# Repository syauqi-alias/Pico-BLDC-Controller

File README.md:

# Pico-BLDC-Controller

This project documents the design of a custom Brushless DC (BLDC) motor controller for a hotplate magnetic stirrer, intended for integration with an Opentrons automated liquid handling robot at the Manufacturing Future Lab, University College London.

---

## Project Overview

The primary goal is to create an open-source, accessible, and robust controller for a **260W 30V/7A Maxon BLDC motor**. This is my first venture into designing a motor controller, especially one involving a three-phase half-bridge topology. The journey is as much about learning as it is about the final product.

---

## Hardware Design

The schematic design is functionally complete and is currently undergoing peer review. The component selection process prioritized simplicity and a reduced component count to make the design easier to understand and replicate.

### Key Components:

* **Microcontroller:** **Raspberry Pi RP2350**
    * Chosen for its straightforward development environment and strong community support. While the ADC conversion speed can be a limitation for high-performance Field-Oriented Control (FOC), the goal is to create a baseline design that the open-source community can build upon and optimize.

* **Pre-driver:** **Texas Instruments DRV8350S**
    * This integrated gate driver significantly simplifies the design by handling much of the complexity associated with driving MOSFETs, such as the need for external charge pumps or bootstrap components. It reduces the overall component count and circuit complexity.

* **Motor:** **Maxon EC 90 flat Ø90 mm, brushless, 260 W, with Hall sensors**
    * A powerful 260W brushless motor, providing more than enough torque for stirring viscous solutions.

---

## Software and Firmware

The initial firmware will be developed using the **[simpleFOC](https://simplefoc.com/)** library to accelerate development and establish a functional baseline.

Once the hardware is validated, a longer-term goal is to develop custom firmware from scratch to fully optimize the controller's performance for this specific application.

---

## Current Status

**Status:** In Development (Last Updated: 29/08/2025)

* [x] Component selection finalized.
* [x] Initial schematic design complete.
* [x] Schematic peer review in progress.
* [x] PCB layout design.
* [X] PCB peer review 
* [X] Send out PCB to manufacturer
* [ ] Prototyping and hardware testing.
* [ ] Firmware development.

I'm actively seeking feedback on the schematic from colleagues and online forums. The design has evolved significantly through this iterative process, and I'll continue to post updates as the project progresses.

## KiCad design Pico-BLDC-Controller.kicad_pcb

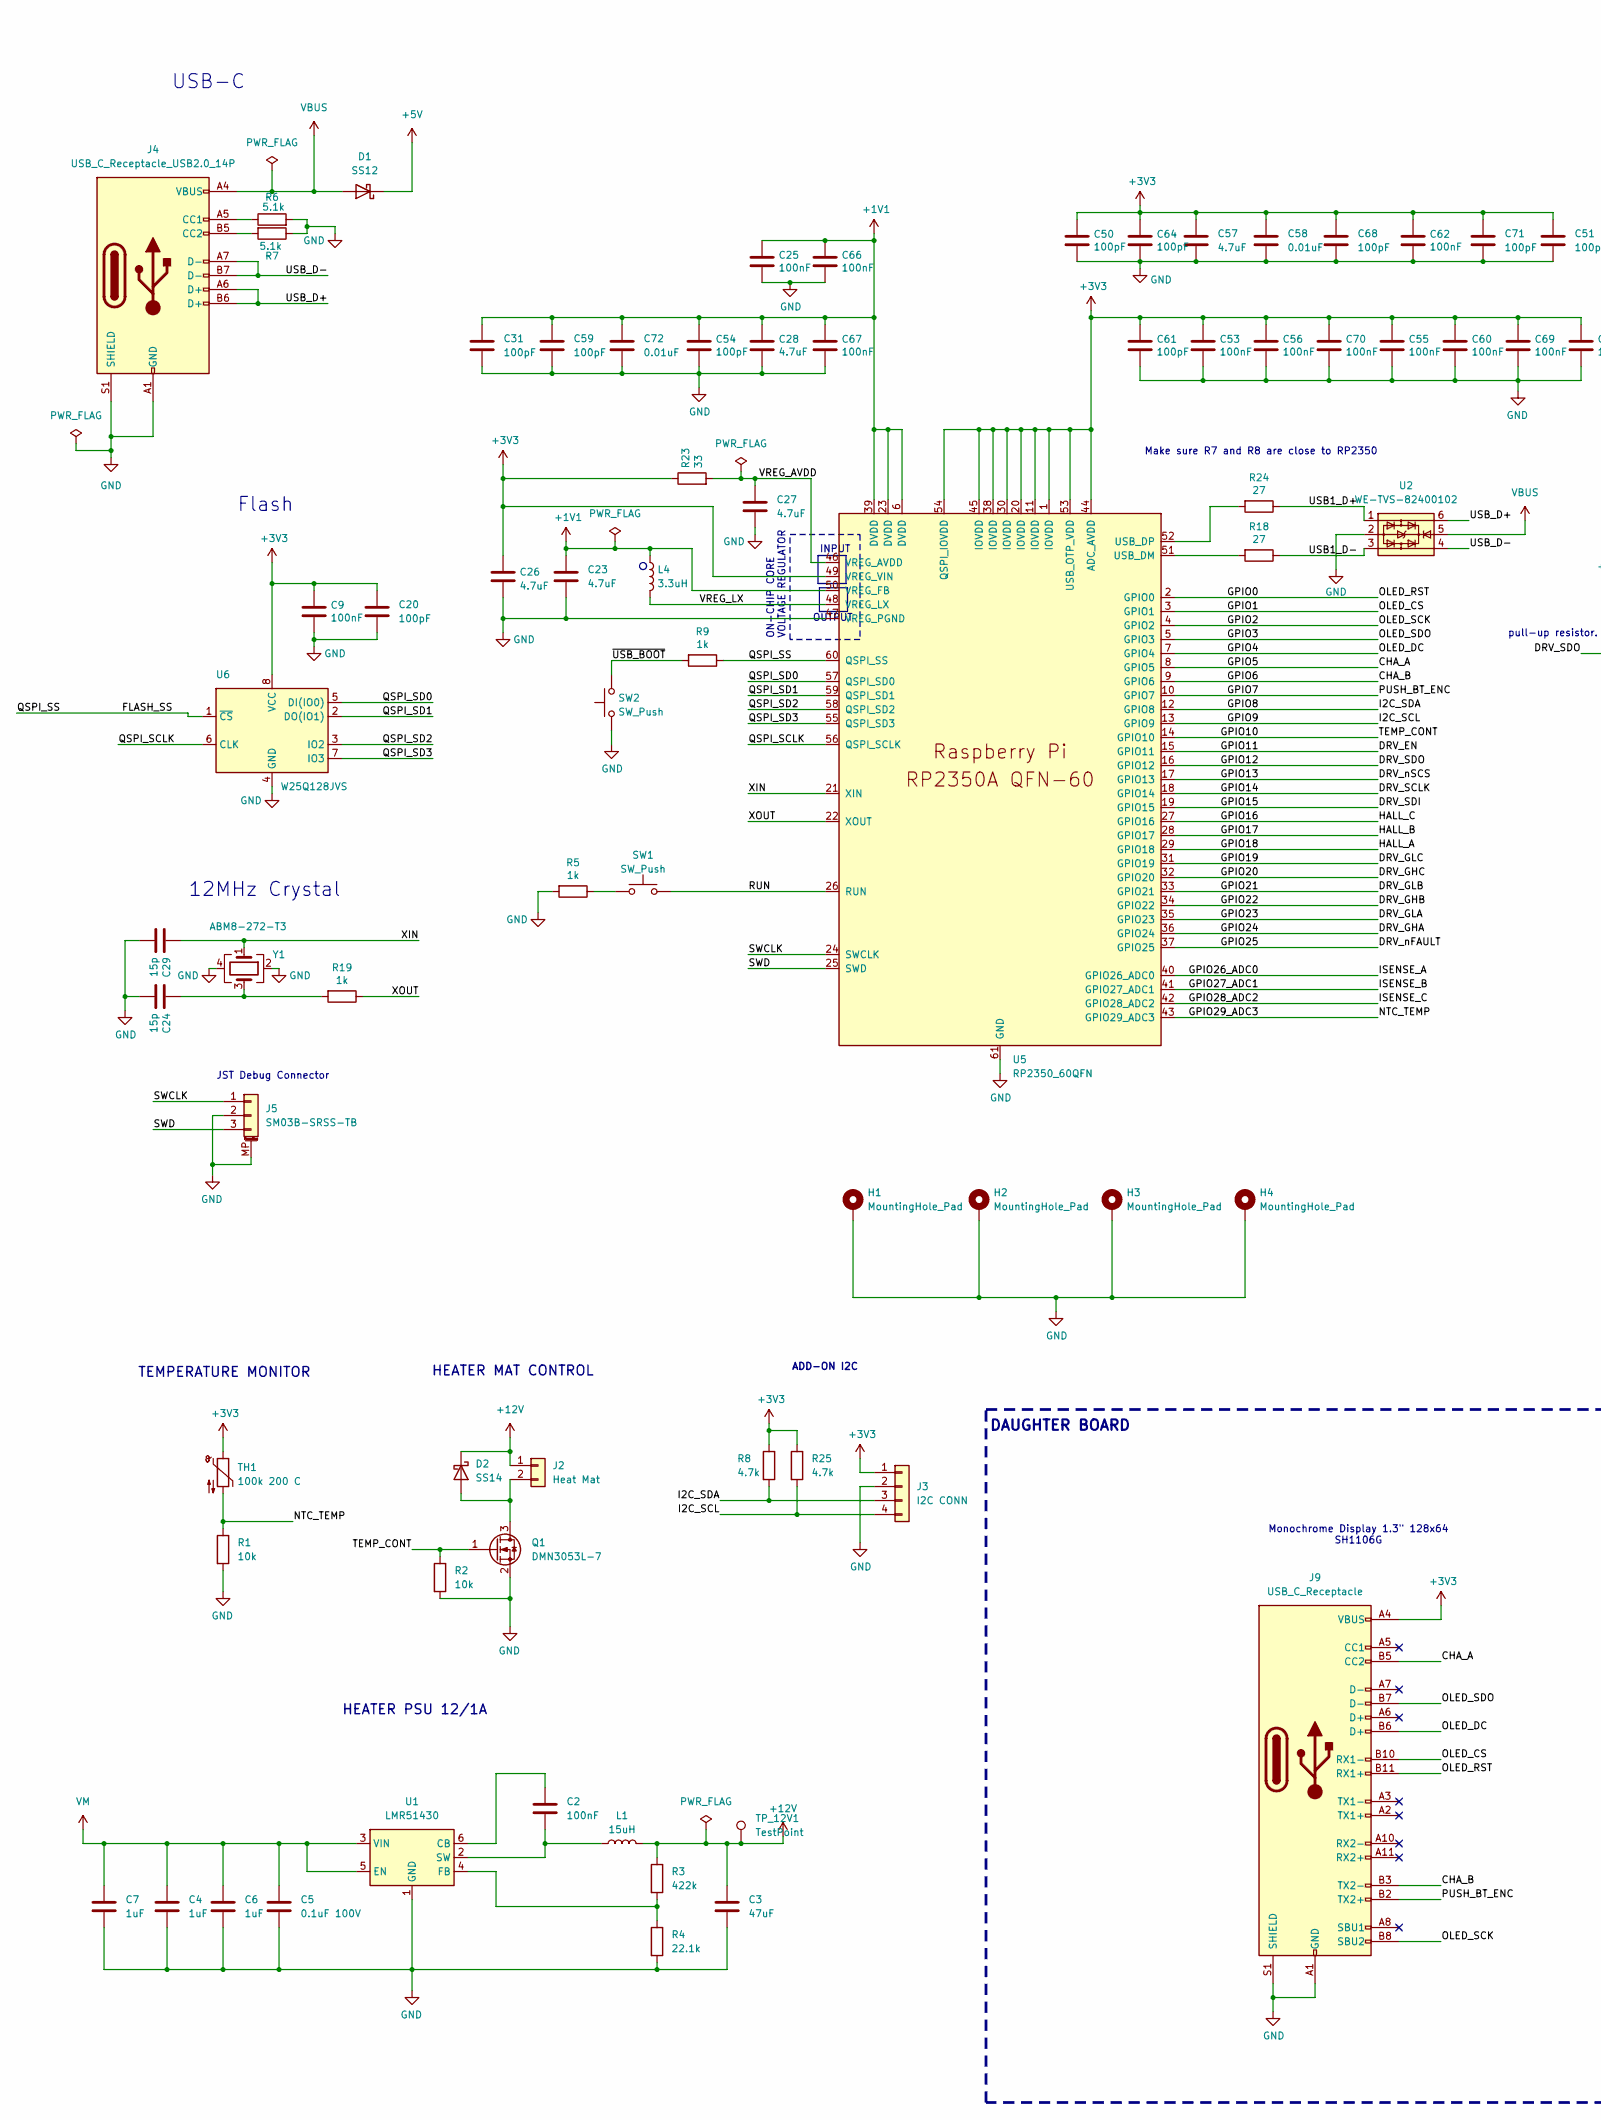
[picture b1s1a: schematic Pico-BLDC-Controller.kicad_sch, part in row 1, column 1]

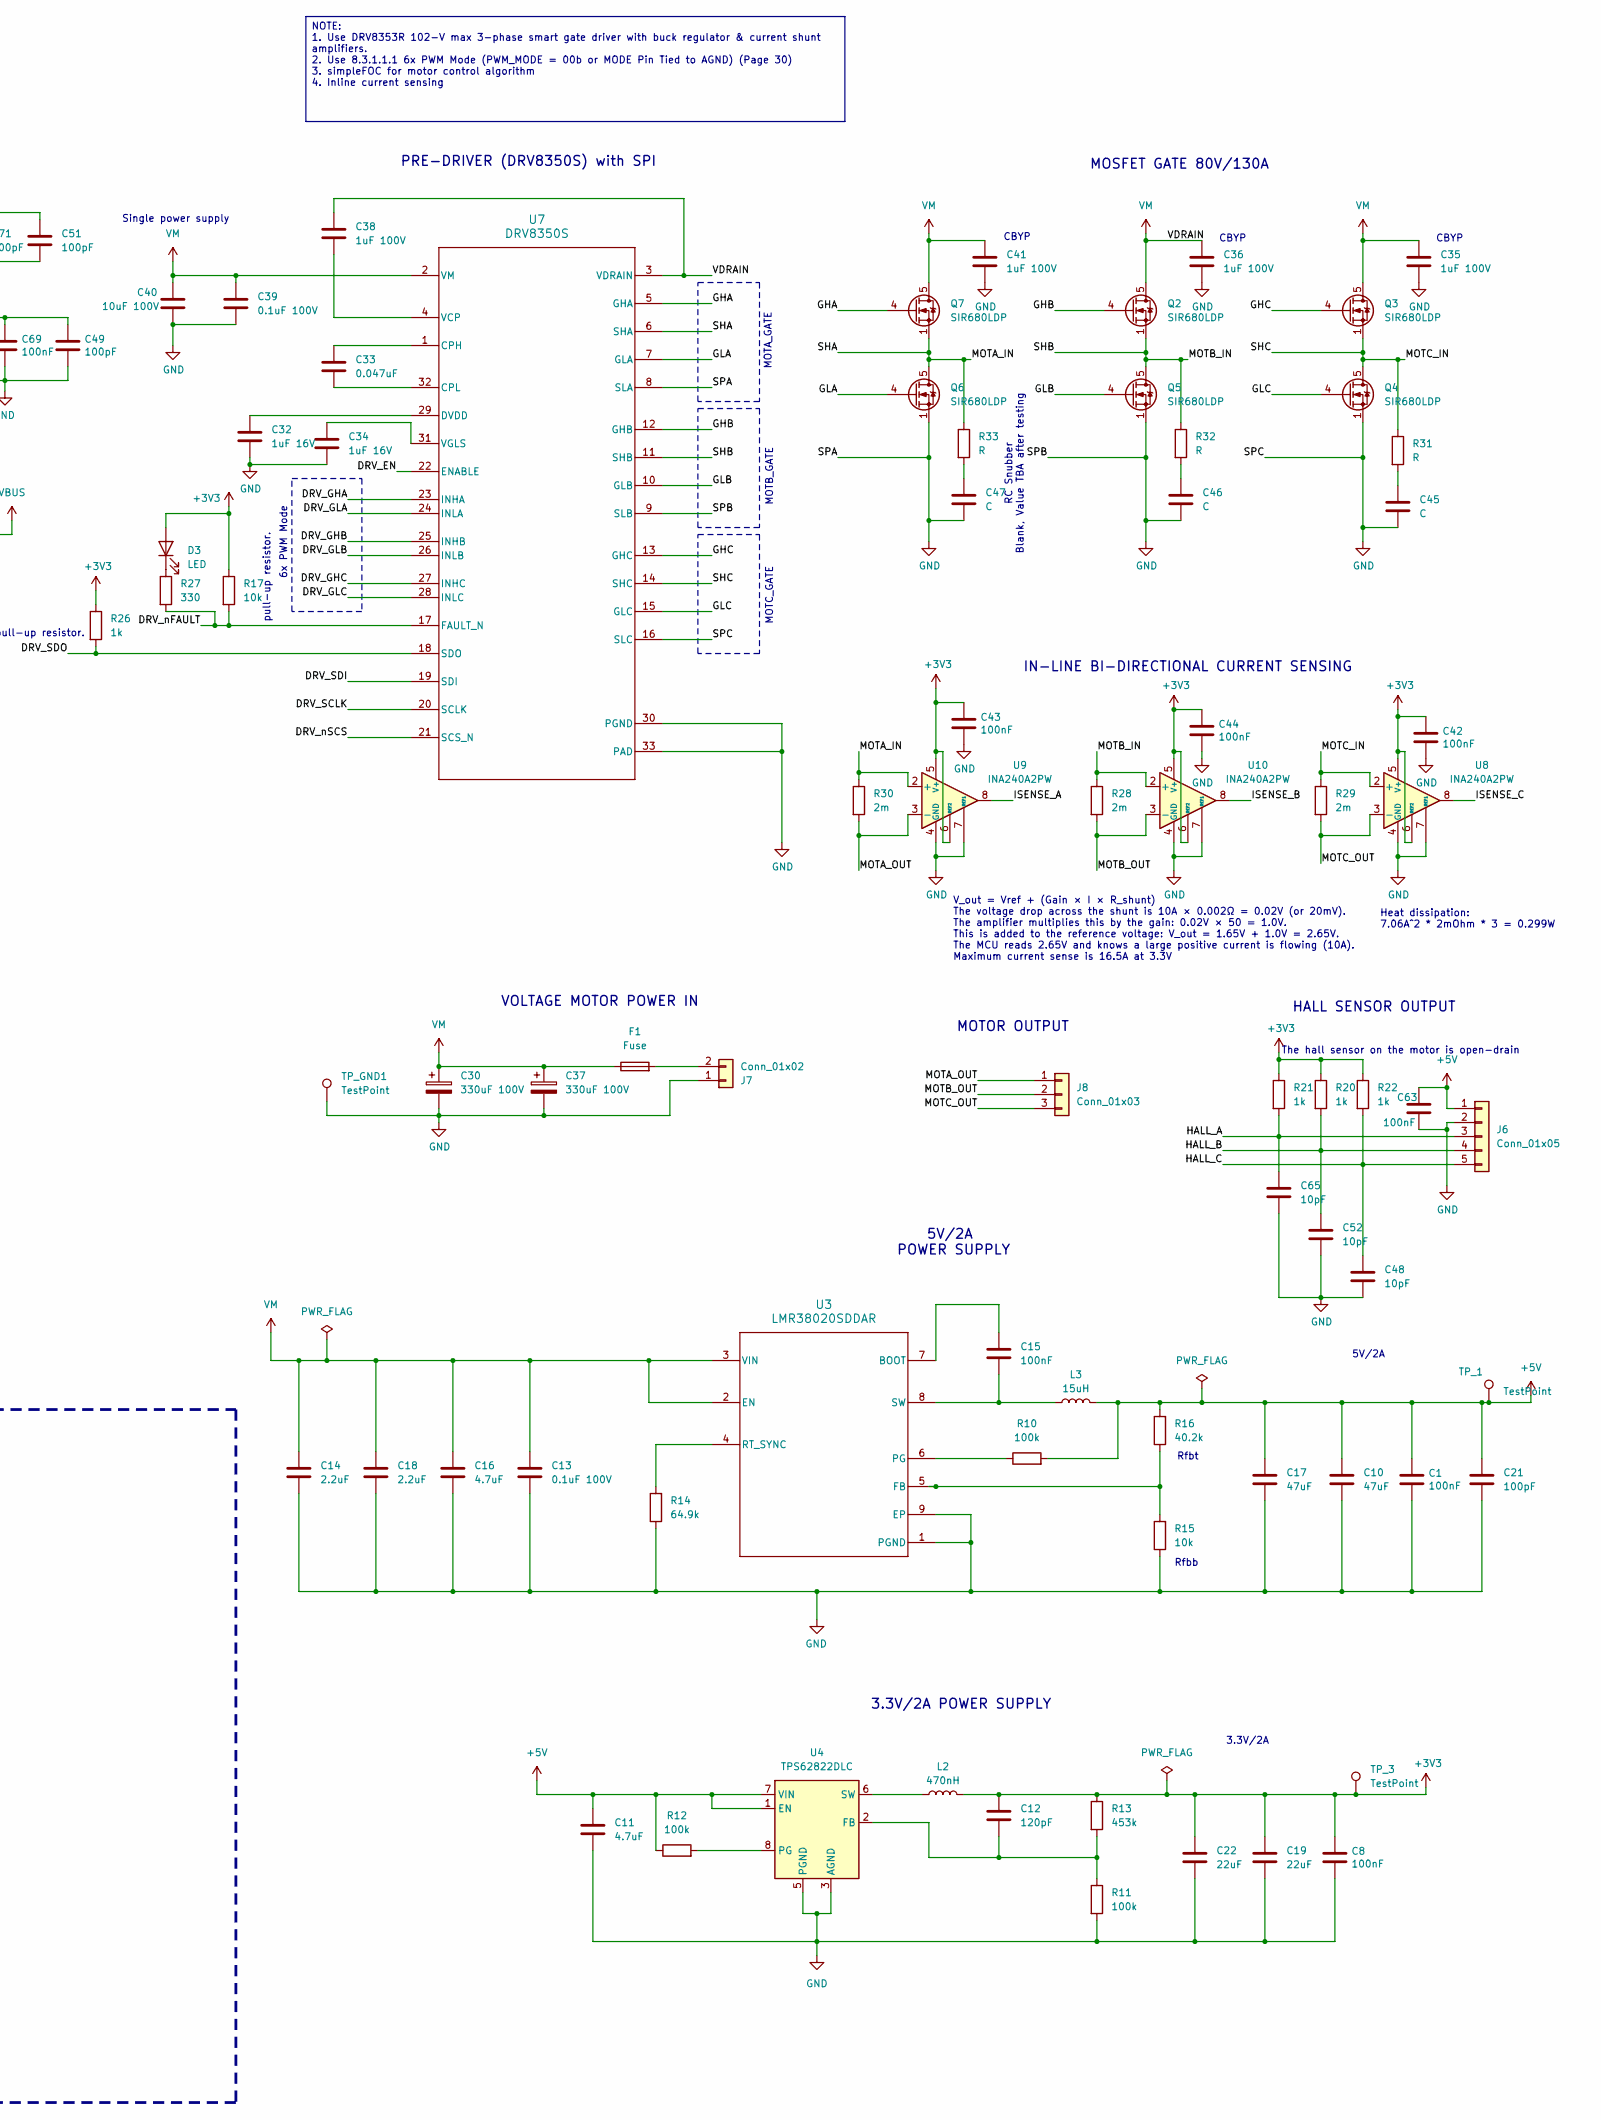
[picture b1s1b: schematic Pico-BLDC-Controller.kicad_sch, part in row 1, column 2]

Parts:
C1, C2, C8, C9, C15, C25, C42, C43, C44, C53, C55, C56, C60, C62, C63, C66, C67, C69, C70: 100nF; C_0603_1608Metric_Pad1.08x0.95mm_HandSolder; MPN C0603C104K5RACAUTO
C3, C10, C17: 47uF; C_1210_3225Metric_Pad1.33x2.70mm_HandSolder; MPN GRM32ER61C476KE15L
C4, C6, C7: 1uF; R_0603_1608Metric_Pad0.98x0.95mm_HandSolder; MPN GRM188D72A105KE01J
C5, C13, C39: 0.1uF 100V; C_0603_1608Metric_Pad1.08x0.95mm_HandSolder; MPN HMK107B7104KAHT
C11, C23, C26, C27, C28: 4.7uF; C_0603_1608Metric_Pad1.08x0.95mm_HandSolder; MPN MCASL168BD7475KTCA01
C12: 120pF; C_0603_1608Metric_Pad1.08x0.95mm_HandSolder; MPN KGM15ACG1H121JT
C14, C18: 2.2uF; C_1210_3225Metric; MPN HMK325B7225KN-T
C16: 4.7uF; C_1210_3225Metric; MPN KAM32LR72A475KU
C19, C22: 22uF; C_0603_1608Metric_Pad1.08x0.95mm_HandSolder; MPN GRM188R60J226MEA0D
C20, C31, C49, C50, C51, C54, C59, C61, C64, C68, C71: 100pF; C_0603_1608Metric_Pad1.08x0.95mm_HandSolder; MPN 0603YC101KAT2A
C21: 100pF; C_0603_1608Metric_Pad1.08x0.95mm_HandSolder; MPN C0402C101K3RACAUTO
C24, C29: 15p; C_0603_1608Metric_Pad1.08x0.95mm_HandSolder; MPN 06033A150JAT2A
C30, C37: 330uF 100V; EEEFK0J103SM; MPN EEV-FK2A331M
C32, C34: 1uF 16V; C_0603_1608Metric_Pad1.08x0.95mm_HandSolder; MPN GXT188R71C105KE13D
C33: 0.047uF; C_0805_2012Metric_Pad1.18x1.45mm_HandSolder; MPN C2012X7R2A473K125AA
C35, C36, C38, C41: 1uF 100V; C_1206_3216Metric; MPN CL31B105KCHNNNE
C40: 10uF 100V; C_2220_5750Metric_Pad1.97x5.40mm_HandSolder; MPN CGA9N3X7S2A106K230KE
C45, C46, C47: C; C_0603_1608Metric_Pad1.08x0.95mm_HandSolder
C48, C52, C65: 10pF; C_0603_1608Metric_Pad1.08x0.95mm_HandSolder; MPN 06033A100KAT2A
C57: 4.7uF; C_0603_1608Metric_Pad1.08x0.95mm_HandSolder; MPN KGM15BR50J475KT
C58, C72: 0.01uF; C_0603_1608Metric_Pad1.08x0.95mm_HandSolder; MPN GCM188R71H103KA37J
D1: SS12; D_SMA; MPN SS12
D2: SS14; D_SMA; MPN SS14
D3: LED; LED_0603_1608Metric_Pad1.05x0.95mm_HandSolder
F1: Fuse; Fuse_Schurter_UMZ250; MPN 0463030.ER
H1, H2, H3, H4: MountingHole_Pad; MountingHole_2.2mm_M2_DIN965_Pad_TopBottom
J2: Heat Mat; Molex_KK-254_AE-6410-02A_1x02_P2.54mm_Vertical; MPN 217796-1021
J3: I2C CONN; Molex_KK-254_AE-6410-04A_1x04_P2.54mm_Vertical; MPN 22-11-2042
J4: USB_C_Receptacle_USB2.0_14P; USB_C_Receptacle_HRO_TYPE-C-31-M-12; MPN TYPE-C-31-M-12
J5: SM03B-SRSS-TB; JST_SH_SM03B-SRSS-TB_1x03-1MP_P1.00mm_Horizontal; MPN SM03B-SRSS-TB(LF)(SN)
J6: Conn_01x05; Molex_KK-254_AE-6410-05A_1x05_P2.54mm_Vertical; MPN 22-11-2052
J7: Conn_01x02; AMASS_XT30U-M_1x02_P5.0mm_Vertical; MPN XT30U-M
J8: Conn_01x03; AMASS_MR30PW-FB_1x03_P3.50mm_Horizontal; MPN MR30PW-F20.G.Y
J9: USB_C_Receptacle; USB_C_Receptacle_JAE_DX07S024WJ3R400
L1: 15uH; L_Coilcraft_MSS1210-XXX; MPN MSS1210-153MED
L2: 470nH; L_Wurth_WE-LQSH-2010; MPN 74479275147
L3: 15uH; L_Coilcraft_MSS1038-XXX; MPN MSS1038-153MLB
L4: 3.3uH; L_pol_2016; MPN AOTA-B201610S3R3-101-T
Q1: DMN3053L-7; SOT-23; MPN DMN3053L-7
Q2, Q3, Q4, Q5, Q6, Q7: SIR680LDP; PowerPAK_SO-8_Single; MPN SIR680LDP
R1, R2, R17: 10k; R_0603_1608Metric_Pad0.98x0.95mm_HandSolder; MPN AC0603JR-7W10KL
R3: 422k; R_0603_1608Metric_Pad0.98x0.95mm_HandSolder; MPN ERJ-3EKF4223V
R4: 22.1k; R_0603_1608Metric_Pad0.98x0.95mm_HandSolder; MPN CRCW060322K1FKEBC
R5, R9, R19, R20, R21, R22, R26: 1k; R_0603_1608Metric_Pad0.98x0.95mm_HandSolder; MPN RC0603FR-101KL
R6, R7: 5.1k; R_0603_1608Metric_Pad0.98x0.95mm_HandSolder; MPN CR0603-FX-5101ELF
R8, R25: 4.7k; R_0603_1608Metric_Pad0.98x0.95mm_HandSolder; MPN RC0603FR-7W4K7L
R10, R11: 100k; R_0603_1608Metric_Pad0.98x0.95mm_HandSolder; MPN CRCW0603100KFKEA
R12: 100k; R_0603_1608Metric; MPN ERJ-PB3B1003V
R13: 453k; R_0603_1608Metric_Pad0.98x0.95mm_HandSolder; MPN CR0603-FX-4533ELF
R14: 64.9k; R_0603_1608Metric_Pad0.98x0.95mm_HandSolder; MPN CRCW060364K9FKEA
R15: 10k; R_0603_1608Metric_Pad0.98x0.95mm_HandSolder; MPN CRCW060310K0FKEI
R16: 40.2k; R_0603_1608Metric_Pad0.98x0.95mm_HandSolder; MPN CR0603-FX-4022ELF
R18, R24: 27; R_0603_1608Metric_Pad0.98x0.95mm_HandSolder; MPN CR0603-JW-270ELF
R23: 33; R_0603_1608Metric_Pad0.98x0.95mm_HandSolder; MPN AC0603DR-0733RL
R27: 330; R_0603_1608Metric; MPN CRCW0603330RFKEC
R28, R29, R30: 2m; R_2512_6332Metric_Pad1.40x3.35mm_HandSolder; MPN WSLP25122L000FEA
R31, R32, R33: R; R_0805_2012Metric_Pad1.20x1.40mm_HandSolder
SW1, SW2: SW_Push; SW_Push_1P1T_NO_Vertical_Wuerth_434133025816; MPN 434133025816
TH1: 100k 200 C; PinSocket_1x02_P2.54mm_Vertical; MPN B57560G1104F000
TP_1, TP_3, TP_12V1: TestPoint; TestPoint_Pad_D1.0mm
TP_GND1: TestPoint; TestPoint_Pad_D1.0mm
U1: LMR51430; SOT-23-6; MPN LMR51430YFDDCR
U2: WE-TVS-82400102; SOT-23-6; MPN 82400102
U3: LMR38020SDDAR; DDA0008E-MFG; MPN LMR38020SDDAR
U4: TPS62822DLC; Texas_VSON-HR-8_1.5x2mm_P0.5mm; MPN TPS62822DLCR
U5: RP2350_60QFN; RP2350-QFN-60-1EP_7x7_P0.4mm_EP3.4x3.4mm_ThermalVias; MPN SC1509(13)
U6: W25Q128JVS; SOIC-8_5.3x5.3mm_P1.27mm; MPN W25Q128JVSIM TR
U7: DRV8350S; RTV0032E; MPN DRV8350SRTVT
U8, U9, U10: INA240A2PW; TSSOP-8_4.4x3mm_P0.65mm; MPN INA240A2PWR
Y1: ABM8-272-T3; Crystal_SMD_3225-4Pin_3.2x2.5mm; MPN ABM8-272-T3

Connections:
+1V1: C23.1, C25.1, C28.1, C31.1, C54.1, C59.1, C66.1, C67.1, C72.1, L4.1, U5.6 (DVDD), U5.23 (DVDD), U5.39 (DVDD), U5.50 (VREG_FB)
+3V3: C8.1, C9.1, C12.1, C19.1, C20.1, C22.1, C26.1, C42.1, C43.1, C44.1, C49.1, C50.1, C51.1, C53.1, C55.1, C56.1, C57.1, C58.1, C60.1, C61.1, C62.1, C64.1, C68.1, C69.1, C70.1, C71.1, D3.2 (A), J3.1, J9.A4 (VBUS), J9.A9 (VBUS), J9.B4 (VBUS), J9.B9 (VBUS), L2.2, R8.1, R13.1, R17.1, R20.1, R21.1, R22.1, R23.1, R25.1, R26.1, TH1.1, TP_3.1, U5.1 (IOVDD), U5.11 (IOVDD), U5.20 (IOVDD), U5.30 (IOVDD), U5.38 (IOVDD), U5.44 (ADC_AVDD), U5.45 (IOVDD), U5.49 (VREG_VIN), U5.53 (USB_OTP_VDD), U5.54 (QSPI_IOVDD), U6.8 (VCC), U8.5 (V+), U8.6 (REF2), U9.5 (V+), U9.6 (REF2), U10.5 (V+), U10.6 (REF2)
+5V: C1.1, C10.1, C11.1, C17.1, C21.1, C63.1, D1.1 (K), J6.1, L3.2, R10.2, R12.1, R16.2, TP_1.1, U4.1 (EN), U4.7 (VIN)
+12V: C3.1, D2.1 (K), J2.1, L1.2, R3.1, TP_12V1.1
/CHA_A: J9.B5 (CC2), U5.8 (GPIO5)
/CHA_B: J9.B3 (TX2-), U5.9 (GPIO6)
/DRV_EN: U5.15 (GPIO11), U7.22 (ENABLE)
/DRV_GHA: U5.36 (GPIO24), U7.23 (INHA)
/DRV_GHB: U5.34 (GPIO22), U7.25 (INHB)
/DRV_GHC: U5.32 (GPIO20), U7.27 (INHC)
/DRV_GLA: U5.35 (GPIO23), U7.24 (INLA)
/DRV_GLB: U5.33 (GPIO21), U7.26 (INLB)
/DRV_GLC: U5.31 (GPIO19), U7.28 (INLC)
/DRV_SCLK: U5.18 (GPIO14), U7.20 (SCLK)
/DRV_SDI: U5.19 (GPIO15), U7.19 (SDI)
/DRV_SDO: R26.2, U5.16 (GPIO12), U7.18 (SDO)
/DRV_nFAULT: R17.2, R27.2, U5.37 (GPIO25), U7.17 (FAULT_N)
/DRV_nSCS: U5.17 (GPIO13), U7.21 (SCS_N)
/FLASH_SS: R9.1, U5.60 (QSPI_SS), U6.1 (~CS)
/GHA: Q7.4 (G), U7.5 (GHA)
/GHB: Q2.4 (G), U7.12 (GHB)
/GHC: Q3.4 (G), U7.13 (GHC)
/GLA: Q6.4 (G), U7.7 (GLA)
/GLB: Q5.4 (G), U7.10 (GLB)
/GLC: Q4.4 (G), U7.15 (GLC)
/GPIO0: J9.B11 (RX1+), U5.2 (GPIO0)
/GPIO1: J9.B10 (RX1-), U5.3 (GPIO1)
/GPIO2: J9.B8 (SBU2), U5.4 (GPIO2)
/GPIO3: J9.B7 (D-), U5.5 (GPIO3)
/GPIO4: J9.B6 (D+), U5.7 (GPIO4)
/GPIO7: J9.B2 (TX2+), U5.10 (GPIO7)
/GPIO8: J3.3, R8.2, U5.12 (GPIO8)
/GPIO9: J3.4, R25.2, U5.13 (GPIO9)
/GPIO10: Q1.1 (G), R2.1, U5.14 (GPIO10)
/GPIO16: C48.1, J6.5, R22.2, U5.27 (GPIO16)
/GPIO17: C52.1, J6.4, R20.2, U5.28 (GPIO17)
/GPIO18: C65.1, J6.3, R21.2, U5.29 (GPIO18)
/GPIO26_ADC0: U5.40 (GPIO26_ADC0), U9.8
/GPIO27_ADC1: U5.41 (GPIO27_ADC1), U10.8
/GPIO28_ADC2: U5.42 (GPIO28_ADC2), U8.8
/GPIO29_ADC3: R1.1, TH1.2, U5.43 (GPIO29_ADC3)
/MOTA_IN: Q6.5 (D), Q7.1 (S), Q7.2 (S), Q7.3 (S), R30.1, R33.1, U7.6 (SHA), U9.2 (+)
/MOTA_OUT: J8.1, R30.2, U9.3 (-)
/MOTB_IN: Q2.1 (S), Q2.2 (S), Q2.3 (S), Q5.5 (D), R28.1, R32.1, U7.11 (SHB), U10.2 (+)
/MOTB_OUT: J8.2, R28.2, U10.3 (-)
/MOTC_IN: Q3.1 (S), Q3.2 (S), Q3.3 (S), Q4.5 (D), R29.1, R31.1, U7.14 (SHC), U8.2 (+)
/MOTC_OUT: J8.3, R29.2, U8.3 (-)
/QSPI_SCLK: U5.56 (QSPI_SCLK), U6.6 (CLK)
/QSPI_SD0: U5.57 (QSPI_SD0), U6.5 (DI(IO0))
/QSPI_SD1: U5.59 (QSPI_SD1), U6.2 (DO(IO1))
/QSPI_SD2: U5.58 (QSPI_SD2), U6.3 (IO2)
/QSPI_SD3: U5.55 (QSPI_SD3), U6.7 (IO3)
/RUN: SW1.2, U5.26 (RUN)
/SWCLK: J5.1, U5.24 (SWCLK)
/SWD: J5.3, U5.25 (SWD)
/USB1_D+: R24.1, U2.1
/USB1_D-: R18.1, U2.3
/USB_D+: J4.A6 (D+), J4.B6 (D+), U2.6
/USB_D-: J4.A7 (D-), J4.B7 (D-), U2.4
/VREG_AVDD: C27.1, R23.2, U5.46 (VREG_AVDD)
/VREG_LX: L4.2, U5.48 (VREG_LX)
/XIN: C29.1, U5.21 (XIN), Y1.1
/XOUT: R19.1, U5.22 (XOUT)
/~USB_BOOT: R9.2, SW2.2
GND: C1.2, C3.2, C4.2, C5.2, C6.2, C7.2, C8.2, C9.2, C10.2, C11.2, C13.2, C14.2, C16.2, C17.2, C18.2, C19.2, C20.2, C21.2, C22.2, C23.2, C24.2, C25.2, C26.2, C27.2, C28.2, C29.2, C30.2, C31.2, C32.2, C34.2, C35.2, C36.2, C37.2, C39.2, C40.2, C41.2, C42.2, C43.2, C44.2, C45.2, C46.2, C47.2, C48.2, C49.2, C50.2, C51.2, C52.2, C53.2, C54.2, C55.2, C56.2, C57.2, C58.2, C59.2, C60.2, C61.2, C62.2, C63.2, C64.2, C65.2, C66.2, C67.2, C68.2, C69.2, C70.2, C71.2, C72.2, H1.1, H2.1, H3.1, H4.1, J3.2, J4.A1 (GND), J4.A12 (GND), J4.B1 (GND), J4.B12 (GND), J4.S1 (SHIELD), J5.2, J5.MP (MountPin), J6.2, J7.1, J9.A1 (GND), J9.A12 (GND), J9.B1 (GND), J9.B12 (GND), J9.S1 (SHIELD), Q1.2 (S), Q4.1 (S), Q4.2 (S), Q4.3 (S), Q5.1 (S), Q5.2 (S), Q5.3 (S), Q6.1 (S), Q6.2 (S), Q6.3 (S), R1.2, R2.2, R4.2, R5.2, R6.2, R7.1, R11.2, R14.1, R15.1, SW2.1, TP_GND1.1, U1.1 (GND), U2.2, U3.1 (PGND), U3.9 (EP), U3.10, U3.11, U3.12, U3.13, U3.14, U3.15, U4.3 (AGND), U4.5 (PGND), U5.47 (VREG_PGND), U5.61 (GND), U6.4 (GND), U7.8 (SLA), U7.9 (SLB), U7.16 (SLC), U7.30 (PGND), U7.33 (PAD), U8.1 (GND), U8.4 (GND), U8.7 (REF1), U9.1 (GND), U9.4 (GND), U9.7 (REF1), U10.1 (GND), U10.4 (GND), U10.7 (REF1), Y1.2, Y1.4
unnamed: C24.1, R19.2, Y1.3
unnamed: C45.1, R31.2
unnamed: C46.1, R32.2
unnamed: C47.1, R33.2
unnamed: D2.2 (A), J2.2, Q1.3 (D)
unnamed: D3.1 (K), R27.1
unnamed: J4.A5 (CC1), R6.1
unnamed: J4.B5 (CC2), R7.2
unnamed: F1.2, J7.2
unnamed: R5.1, SW1.1
unnamed: C2.1, U1.6 (CB)
unnamed: R3.2, R4.1, U1.4 (FB)
unnamed: C2.2, L1.1, U1.2 (SW)
unnamed: C15.1, U3.7 (BOOT)
unnamed: R15.2, R16.1, U3.5 (FB)
unnamed: R10.1, U3.6 (PG)
unnamed: R14.2, U3.4 (RT_SYNC)
unnamed: C15.2, L3.1, U3.8 (SW)
unnamed: C12.2, R11.1, R13.2, U4.2 (FB)
unnamed: R12.2, U4.8 (PG)
unnamed: L2.1, U4.6 (SW)
unnamed: R18.2, U5.51 (USB_DM)
unnamed: R24.2, U5.52 (USB_DP)
unnamed: C33.1, U7.1 (CPH)
unnamed: C33.2, U7.32 (CPL)
unnamed: C32.1, U7.29 (DVDD)
unnamed: C38.2, U7.4 (VCP)
unnamed: C34.1, U7.31 (VGLS)
VBUS: D1.2 (A), J4.A4 (VBUS), J4.A9 (VBUS), J4.B4 (VBUS), J4.B9 (VBUS), U2.5
VM: C4.1, C5.1, C6.1, C7.1, C13.1, C14.1, C16.1, C18.1, C30.1, C35.1, C36.1, C37.1, C38.1, C39.1, C40.1, C41.1, F1.1, Q2.5 (D), Q3.5 (D), Q7.5 (D), U1.3 (VIN), U1.5 (EN), U3.2 (EN), U3.3 (VIN), U7.2 (VM), U7.3 (VDRAIN)

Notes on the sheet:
CBYP
PRE-DRIVER (DRV8350S) with SPI
3.3V/2A POWER SUPPLY
TEMPERATURE MONITOR
3.3V/2A
Rfbt
Heat dissipation: 7.06A^2 * 2mOhm * 3 = 0.299W
12MHz Crystal
MOTC_GATE
INPUT
MOTOR OUTPUT
Rfbb
Monochrome Display 1.3" 128x64 SH1106G
pull-up resistor.
6x PWM Mode
5V/2A POWER SUPPLY
JST Debug Connector
IN-LINE BI-DIRECTIONAL CURRENT SENSING
HALL SENSOR OUTPUT
RC Snubber Blank, Value TBA after testing
Make sure R7 and R8 are close to RP2350
5V/2A
DAUGHTER BOARD
OUTPUT
HEATER MAT CONTROL
MOTA_GATE
MOSFET GATE 80V/130A
V_out = Vref + (Gain × I × R_shunt) The voltage drop across the shunt is 10A × 0.002Ω = 0.02V (or 20mV). The amplifier multiplies this by the gain: 0.02V × 50 = 1.0V. This is added to the reference voltage: V_out = 1.65V + 1.0V = 2.65V. The MCU reads 2.65V and knows a large positive current is flow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
VOLTAGE MOTOR POWER IN
ADD-ON I2C
USB-C
ON-CHIP CORE VOLTAGE REGULATOR
HEATER PSU 12/1A
Flash
Single power supply
The hall sensor on the motor is open-drain
MOTB_GATE
NOTE: 1. Use DRV8353R 102-V max 3-phase smart gate driver with buck regulator & current shunt amplifiers. 2. Use 8.3.1.1.1 6x PWM Mode (PWM_MODE = 00b or MODE Pin Tied to AGND) (Page 30) 3. simpleFOC for motor control algorithm 4. Inline current sensing

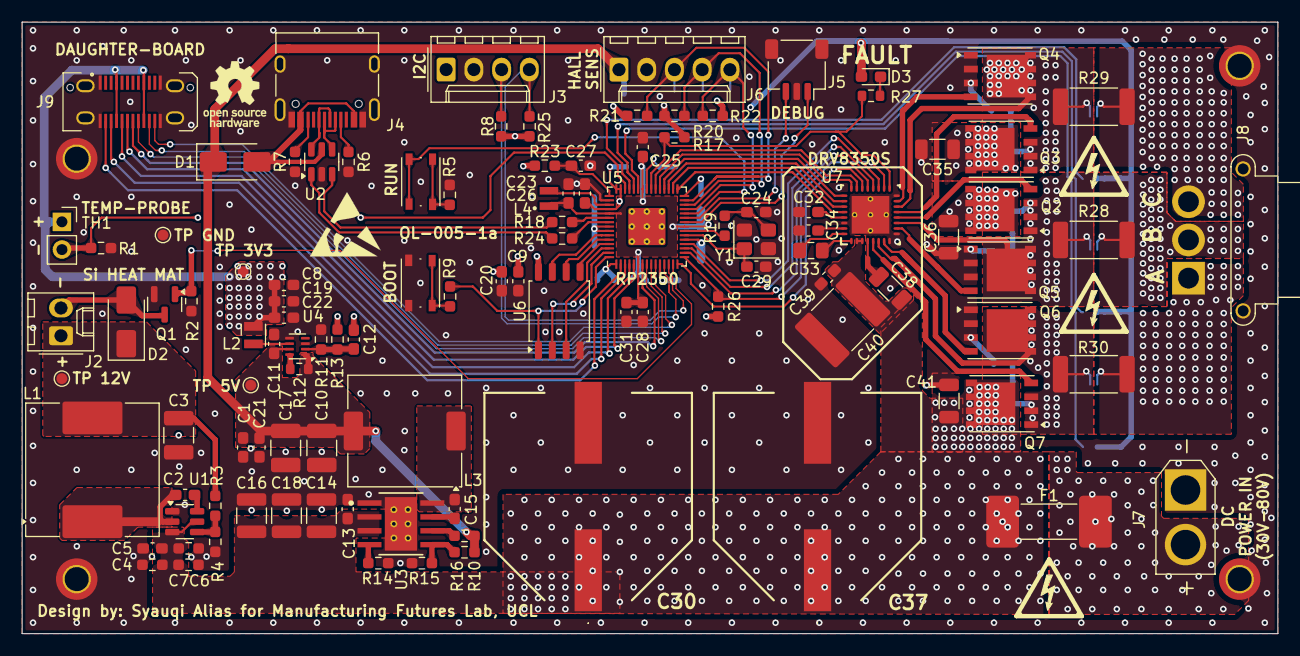
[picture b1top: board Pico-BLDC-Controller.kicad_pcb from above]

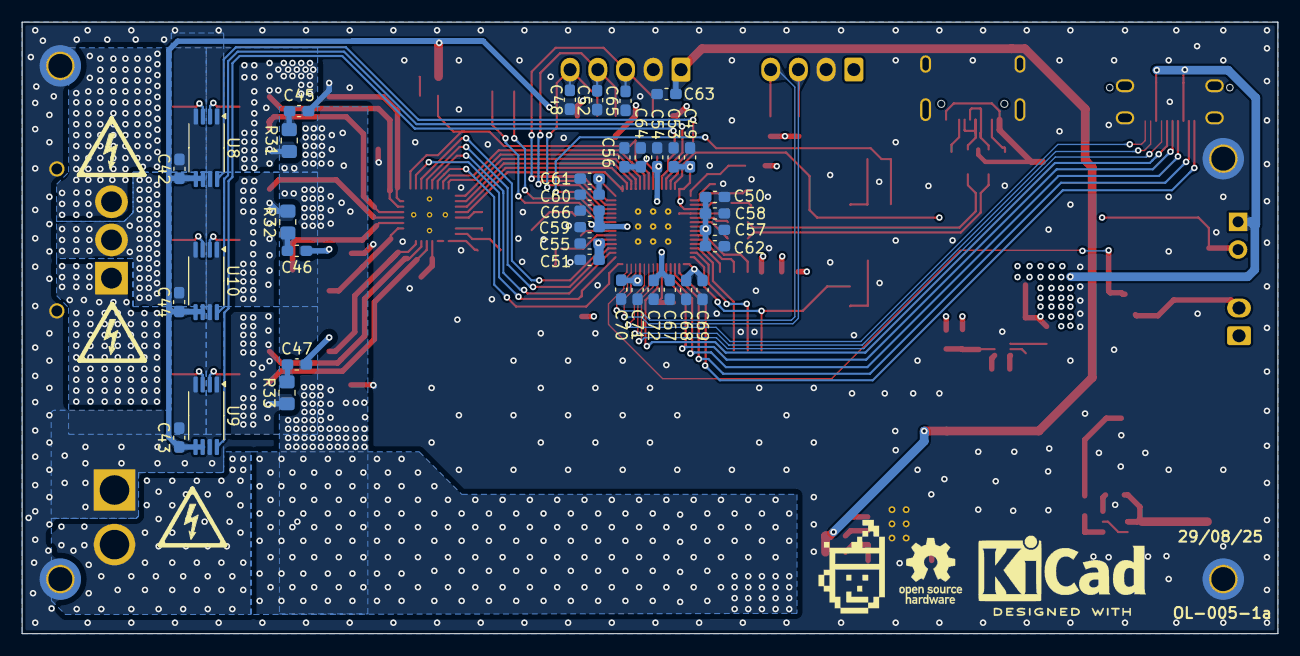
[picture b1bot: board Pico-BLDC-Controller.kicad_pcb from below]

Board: 4 copper layers, 115.0 x 56.0 mm, 150 parts (37 on the bottom side), 95 nets.

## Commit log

2025-07-29 Your commit message
2025-08-19 ingnore backup
2025-08-19 Delete Pico-BLDC-Controller-backups directory
    delete backup
2025-08-19 readme update2
2025-08-27 change connector to usb-c
2025-08-27 update silkscreen
2025-08-27 new pic
2025-08-28 increase board size and more vias
2025-08-29 added date on silkscreen
2025-08-29 add things on README
